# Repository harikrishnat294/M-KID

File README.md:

# M-KID
Macro - Keyboard Input Dial is a free opensource hardware to emulate keyboard / mouse macros.

Simply a dial to send keystrokes repeatedly to the PC like zoom-in, zoom-out OR scroll up and down. etc.

PCB designed in KiCAD. 

Feel free to modify and share your ideas.

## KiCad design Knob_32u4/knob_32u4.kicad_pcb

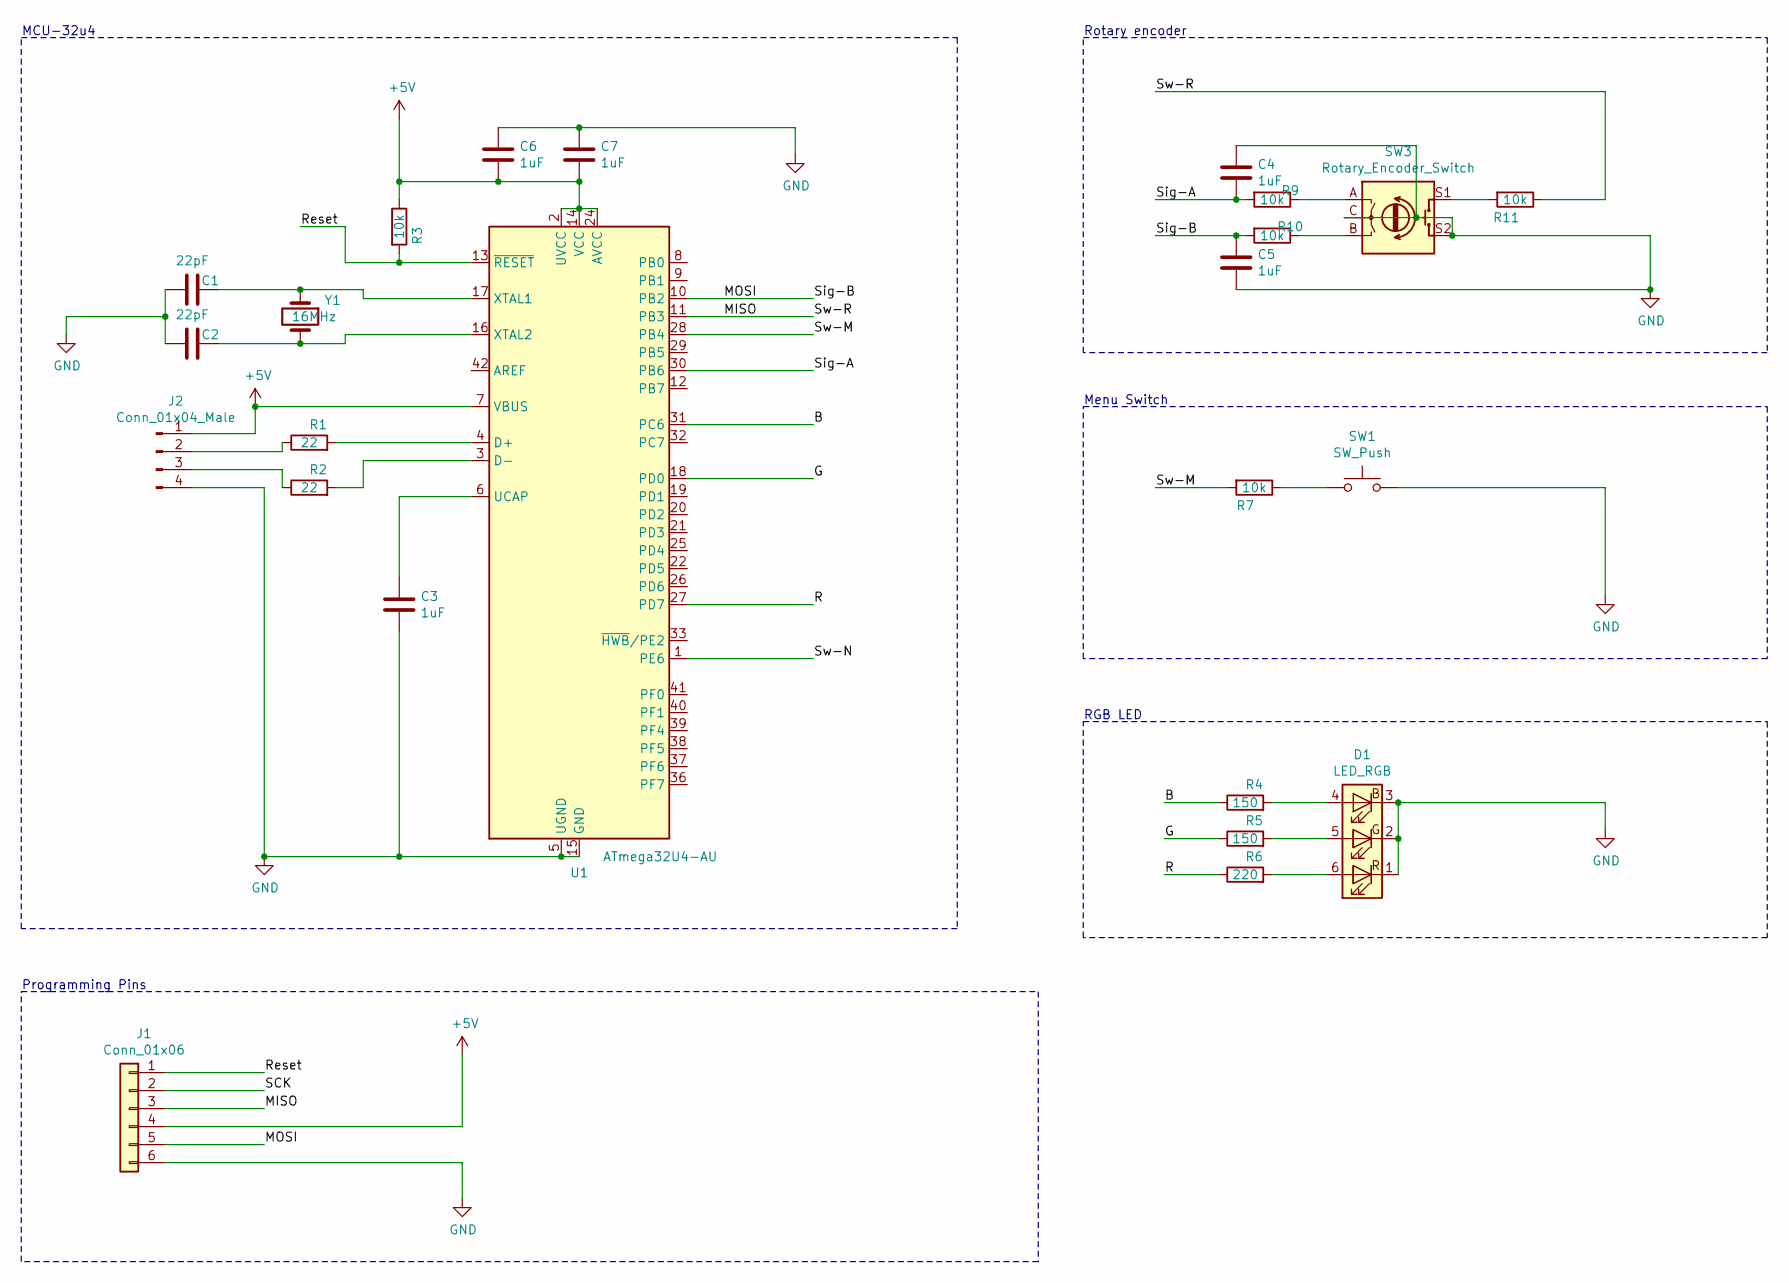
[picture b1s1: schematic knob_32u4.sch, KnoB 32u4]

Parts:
C1, C2: 22pF; C_1206_3216Metric_Pad1.42x1.75mm_HandSolder
C3, C4, C5, C6, C7: 1uF; C_1206_3216Metric_Pad1.42x1.75mm_HandSolder
D1: LED_RGB; LED_RGB_5050-6
J1: Conn_01x06; PinHeader_1x06_P2.54mm_Vertical
J2: Conn_01x04_Male; PinSocket_1x04_P2.54mm_Vertical
R1, R2: 22; R_1206_3216Metric_Pad1.42x1.75mm_HandSolder
R3, R7, R9, R10, R11: 10k; R_1206_3216Metric_Pad1.42x1.75mm_HandSolder
R4, R5: 150; R_1206_3216Metric_Pad1.42x1.75mm_HandSolder
R6: 220; R_1206_3216Metric_Pad1.42x1.75mm_HandSolder
SW1: SW_Push; SW_PUSH_6mm_H8mm
SW3: Rotary_Encoder_Switch; RotaryEncoder_Alps_EC11E-Switch_Vertical_H20mm
U1: ATmega32U4-AU; TQFP-44_10x10mm_P0.8mm
Y1: 16MHz; Crystal_HC49-U_Vertical

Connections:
+5V: C6.1, C7.1, J1.4, J2.1, R3.1, U1.2 (UVCC), U1.7 (VBUS), U1.14 (VCC), U1.24 (AVCC), U1.34 (VCC), U1.44 (AVCC)
/B: R4.1, U1.31 (PC6)
/G: R5.1, U1.18 (PD0)
/MISO: J1.3, R11.1, U1.11 (PB3)
/MOSI: C5.2, J1.5, R10.2, U1.10 (PB2)
/R: R6.1, U1.27 (PD7)
/Reset: J1.1, R3.2, U1.13 (~RESET)
/SCK: J1.2
/Sig-A: C4.1, R9.2, U1.30 (PB6)
/Sw-M: R7.2, U1.28 (PB4)
/Sw-N: U1.1 (PE6)
GND: C1.2, C2.2, C3.1, C4.2, C5.1, C6.2, C7.2, D1.1 (RK), D1.2 (GK), D1.3 (BK), J1.6, J2.4, SW1.2, SW3.C, SW3.S2, U1.5 (UGND), U1.15 (GND), U1.23 (GND), U1.35 (GND), U1.43 (GND)
unnamed: C1.1, U1.17 (XTAL1), Y1.1
unnamed: C2.1, U1.16 (XTAL2), Y1.2
unnamed: C3.2, U1.6 (UCAP)
unnamed: D1.4 (BA), R4.2
unnamed: D1.5 (GA), R5.2
unnamed: D1.6 (RA), R6.2
unnamed: J2.2, R1.1
unnamed: J2.3, R2.1
unnamed: R1.2, U1.4 (D+)
unnamed: R2.2, U1.3 (D-)
unnamed: R7.1, SW1.1
unnamed: R9.1, SW3.A
unnamed: R10.1, SW3.B
unnamed: R11.2, SW3.S1

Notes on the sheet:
Rotary encoder
Menu Switch
RGB LED
MCU-32u4
Programming Pins

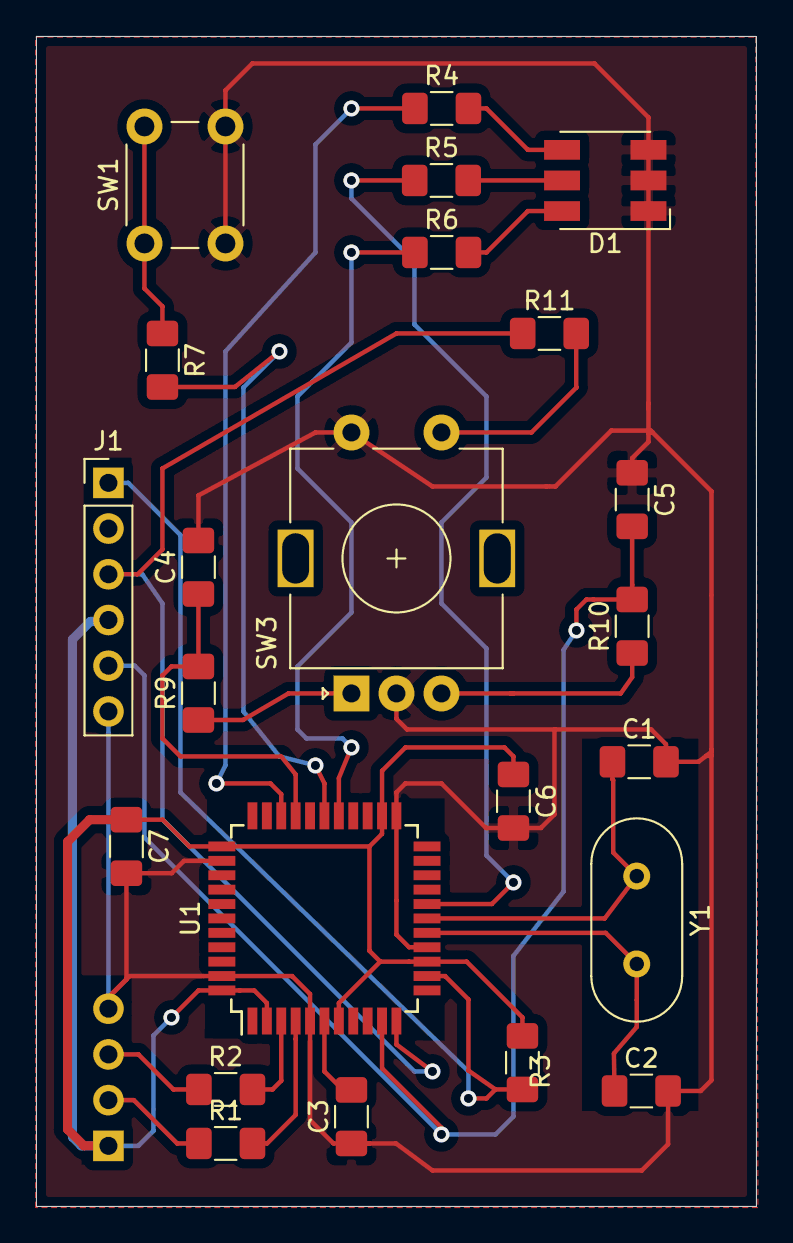
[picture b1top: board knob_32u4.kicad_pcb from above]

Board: 2 copper layers, 40.0 x 65.0 mm, 24 parts (1 on the bottom side), 24 nets.
